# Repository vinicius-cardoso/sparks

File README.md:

# Sparks

A handheld Morse code trainer and radio transmitter.

Press the key. The device times your dots and dashes, walks the Morse tree, and
lights the letter you just formed on a 26-LED panel shaped like the tree itself.
Optionally, it keys a CC1101 and sends the same characters over the air.

The panel is the point. Instead of showing you a decoded letter as text, Sparks
shows you *where that letter lives* in the Morse tree — so the structure of the
code becomes something you read off the board rather than something you memorize
from a table.

## The LED panel

The 26 LEDs are not an arbitrary count — they are the International Morse tree for
the English alphabet, one LED per letter. All **white**, so the panel lights
uniformly.

The dot/dash distinction is carried by the **engraved panel**, not by LED colour:
the arm joining each letter to its parent is etched as a **short mark for a dot**
or a **long bar for a dash**, exactly as in `media/morse_code_guide.png`. The code
for any letter is therefore readable by tracing its path from the centre — and
stays readable with the device switched off.

Layout also follows that image: **E** and **T** sit at the centre, **dots branch
right**, **dashes branch left**, and each deeper level branches perpendicular from
its parent.

```
level 1:  E  T                                     2 LEDs
level 2:  I  A  N  M                               4 LEDs
level 3:  S  U  R  W  D  K  G  O                   8 LEDs
level 4:  H  V  F  ·  L  ·  P  J  B  X  C  Y  Z  Q  ·  ·   12 LEDs
                                                  ──────────
                                                   26 LEDs
```

A full four-level tree has 30 slots. The four marked `·` are the non-English
letters (`..--` Ü, `.-.-` Ä, `---.` Ö, `----` CH) and are left empty — deliberate
gaps in the engraved panel, not mistakes.

## Hardware

| Part | Role |
|---|---|
| ESP32-C3 Supermini | the brain — timing, decoding, radio, everything |
| MAX7219 | LED driver — constant current, 3 pins, no series resistors |
| 26 SMD LEDs | the tree panel — all white |
| CC1101 | 433 MHz transceiver (phase 2) |
| Momentary key | Morse input |
| Buzzer | sidetone, so you hear what you send |
| Li-ion cell + TP4056 | power and charging |

The MAX7219 is **not** programmable — it has no CPU. It holds which LEDs are on
and feeds them regulated current; all decisions happen on the ESP32-C3. It exists
so the panel costs 3 GPIOs instead of 26, and so the board needs **one** current-
setting resistor instead of 26 series resistors.

### Pin budget — 11 of 13 GPIOs

| Function | Pins |
|---|---|
| MAX7219 (DIN, CLK, LOAD) | 3 |
| CC1101 (SCK, MISO, MOSI, CS, GDO0) | 5 |
| Morse key | 1 |
| Buzzer | 1 |
| Battery sense (ADC) | 1 |
| **Total** | **11 — 2 spare** |

See `docs/hardware.md` for the wiring detail and the LED addressing map.

> [!NOTE]
> The MAX7219 is a 5 V part and wants ~3.5 V for a logic high. Driving it from a
> 3.3 V ESP32-C3 often works but is marginal. See `docs/hardware.md` for the two
> fixes (level shifter, or run the chip at ~4 V).

## Build phases

1. **Trainer** — LEDs + key + buzzer. No radio. Fully useful on its own, and
   nothing about it raises regulatory questions.
2. **Radio** — populate the CC1101 once the band and power limits are settled.

The CC1101 footprint is on the board from the start; phase 1 simply leaves it
unpopulated.

## Repository layout

```text
.
├── bom/          # bill of materials
├── docs/         # design decisions, hardware notes
├── firmware/     # Arduino sketch (firmware/sparks/sparks.ino)
├── hardware/     # KiCad project, datasheets
├── mechanical/   # Onshape exports, case STEP/STL
└── media/        # reference images, photos
```

## Toolchain

- **KiCad** for the PCB (`hardware/kicad/`)
- **Onshape** for the case, exported to `mechanical/`
- **Fiber laser** to engrave the copper
- **Arduino** for firmware (`firmware/sparks/`)

Keep editable sources as the source of truth: `.kicad_pro`, `.kicad_sch`,
`.kicad_pcb`, `.ino`, native CAD. Generated manufacturing output belongs in
`exports/` directories.

## Status

Early. The existing sketch (`firmware/sparks/sparks.ino`) is a CC1101 bench test
that sends a hardcoded "HELLO" — it predates the panel design and does not yet
decode input or drive the MAX7219.

## Licence

GPL-3.0 — see `LICENSE`.

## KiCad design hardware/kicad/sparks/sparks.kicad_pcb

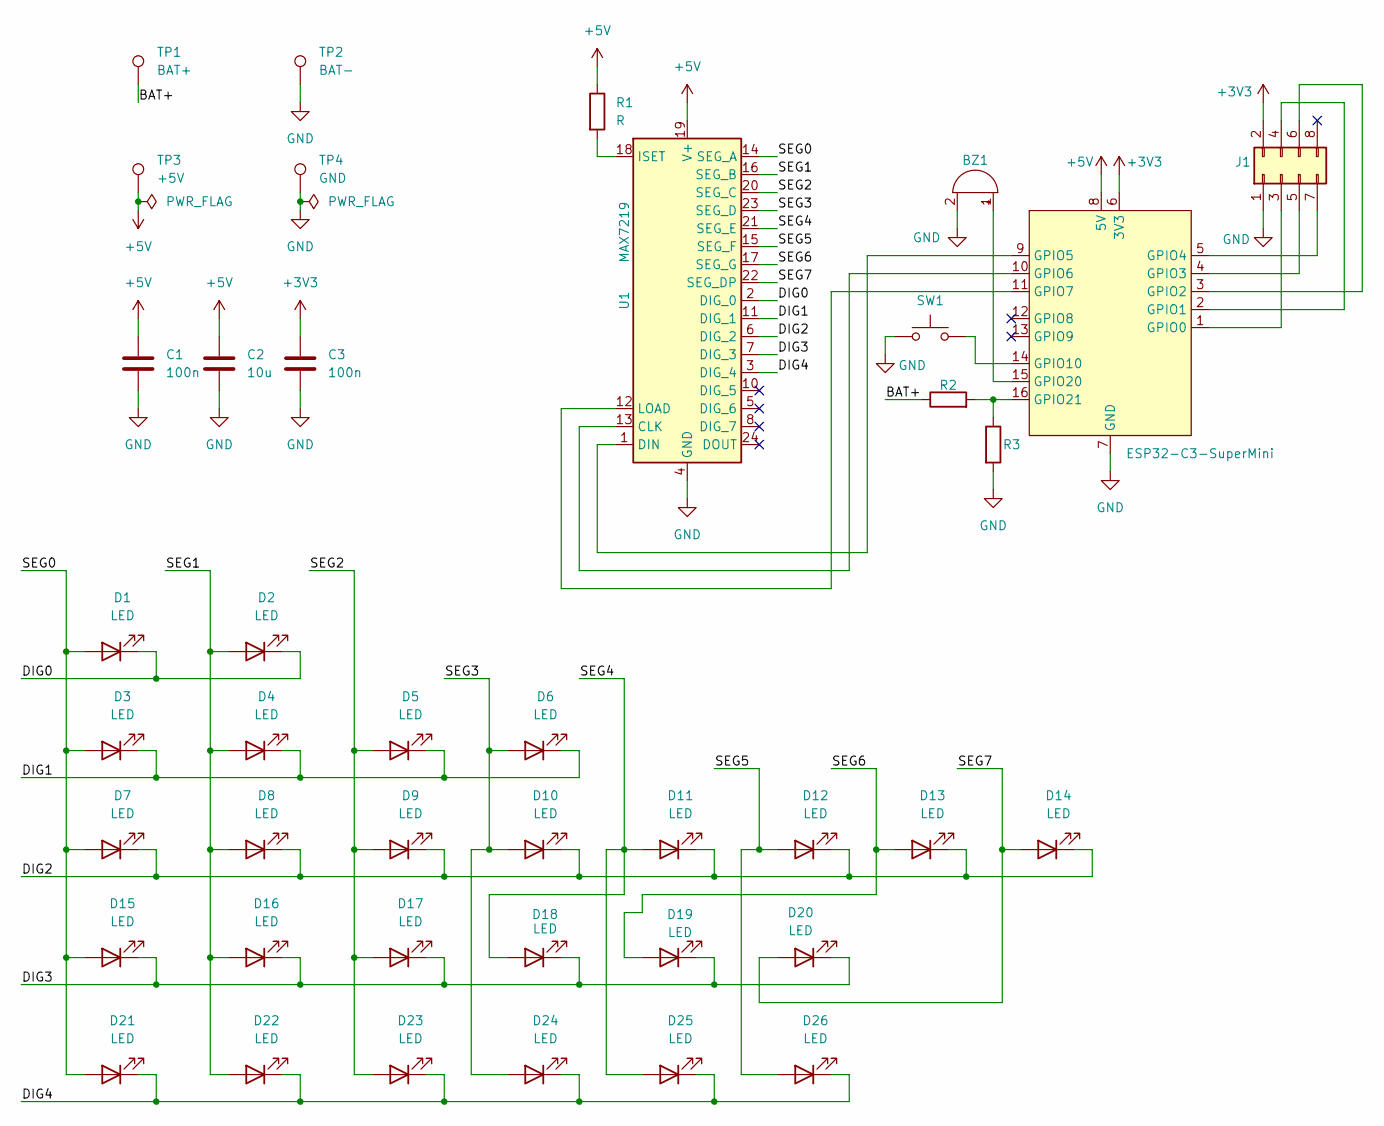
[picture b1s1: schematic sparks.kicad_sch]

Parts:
BZ1: Buzzer; Buzzer_12x9.5RM7.6
C1, C3: 100n; C_0805_2012Metric_Pad1.18x1.45mm_HandSolder
C2: 10u; C_0805_2012Metric_Pad1.18x1.45mm_HandSolder
D1, D2, D3, D4, D5, D6, D7, D8, D9, D10, D11, D12, D13, D14, D15, D16, D17, D18, D19, D20, D21, D22, D23, D24, D25, D26: LED; LED_0805_2012Metric_Pad1.15x1.40mm_HandSolder
J1: Conn_02x04_Odd_Even; PinHeader_2x04_P2.54mm_Vertical
R1: R; R_0805_2012Metric_Pad1.20x1.40mm_HandSolder
R2, R3: 220k; R_0805_2012Metric_Pad1.20x1.40mm_HandSolder
SW1: SW_Push; SW_PUSH_6mm
TP1: BAT+; TestPoint_THTPad_2.0x2.0mm_Drill1.0mm
TP2: BAT-; TestPoint_THTPad_2.0x2.0mm_Drill1.0mm
TP3: +5V; TestPoint_THTPad_2.0x2.0mm_Drill1.0mm
TP4: GND; TestPoint_THTPad_2.0x2.0mm_Drill1.0mm
U1: MAX7219; SOIC-24W_7.5x15.4mm_P1.27mm
U2: ESP32-C3-SuperMini

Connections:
+3V3: C3.1, J1.2, U2.6 (3V3)
+5V: C1.1, C2.1, R1.1, TP3.1 (1_1), U1.19 (V+), U2.8 (5V)
/BAT+: R2.1, TP1.1 (1_1)
/DIG0: D1.1 (K), D2.1 (K), U1.2 (DIG_0)
/DIG1: D3.1 (K), D4.1 (K), D5.1 (K), D6.1 (K), U1.11 (DIG_1)
/DIG2: D7.1 (K), D8.1 (K), D9.1 (K), D10.1 (K), D11.1 (K), D12.1 (K), D13.1 (K), D14.1 (K), U1.6 (DIG_2)
/DIG3: D15.1 (K), D16.1 (K), D17.1 (K), D18.1 (K), D19.1 (K), D20.1 (K), U1.7 (DIG_3)
/DIG4: D21.1 (K), D22.1 (K), D23.1 (K), D24.1 (K), D25.1 (K), D26.1 (K), U1.3 (DIG_4)
/SEG0: D1.2 (A), D3.2 (A), D7.2 (A), D15.2 (A), D21.2 (A), U1.14 (SEG_A)
/SEG1: D2.2 (A), D4.2 (A), D8.2 (A), D16.2 (A), D22.2 (A), U1.16 (SEG_B)
/SEG2: D5.2 (A), D9.2 (A), D17.2 (A), D23.2 (A), U1.20 (SEG_C)
/SEG3: D6.2 (A), D10.2 (A), D24.2 (A), U1.23 (SEG_D)
/SEG4: D11.2 (A), D18.2 (A), D25.2 (A), U1.21 (SEG_E)
/SEG5: D12.2 (A), D26.2 (A), U1.15 (SEG_F)
/SEG6: D13.2 (A), D19.2 (A), U1.17 (SEG_G)
/SEG7: D14.2 (A), D20.2 (A), U1.22 (SEG_DP)
GND: BZ1.2 (-), C1.2, C2.2, C3.2, J1.1, R3.2, SW1.1, TP2.1 (1_1), TP4.1 (1_1), U1.4 (GND), U1.9 (GND), U2.7 (GND)
unnamed: BZ1.1 (+), U2.15 (GPIO20)
unnamed: J1.3, U2.1 (GPIO0)
unnamed: J1.4, U2.2 (GPIO1)
unnamed: J1.5, U2.4 (GPIO3)
unnamed: J1.6, U2.3 (GPIO2)
unnamed: J1.7, U2.5 (GPIO4)
unnamed: U1.13 (CLK), U2.10 (GPIO6)
unnamed: U1.1 (DIN), U2.9 (GPIO5)
unnamed: R1.2, U1.18 (ISET)
unnamed: U1.12 (LOAD), U2.11 (GPIO7)
unnamed: SW1.2, U2.14 (GPIO10)
unnamed: R2.2, R3.1, U2.16 (GPIO21)

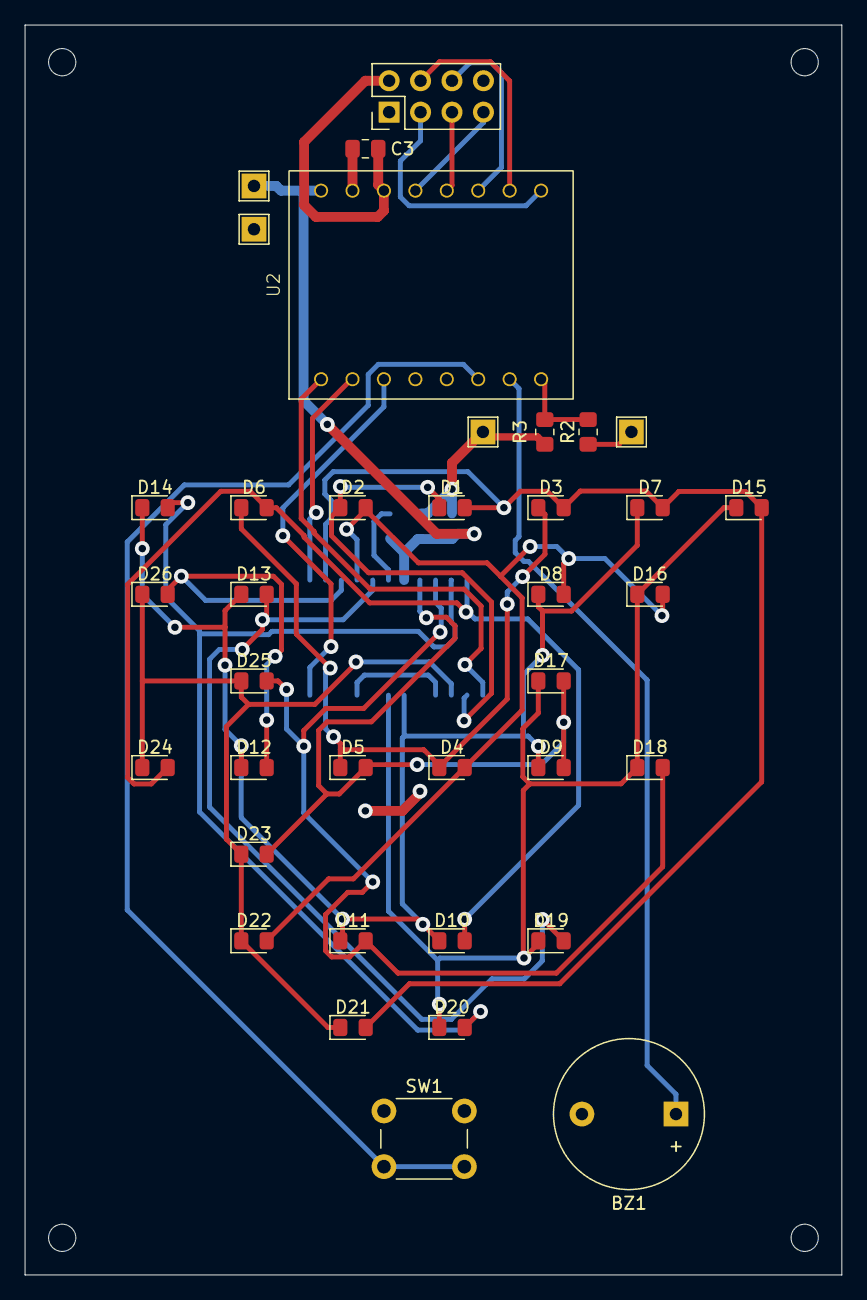
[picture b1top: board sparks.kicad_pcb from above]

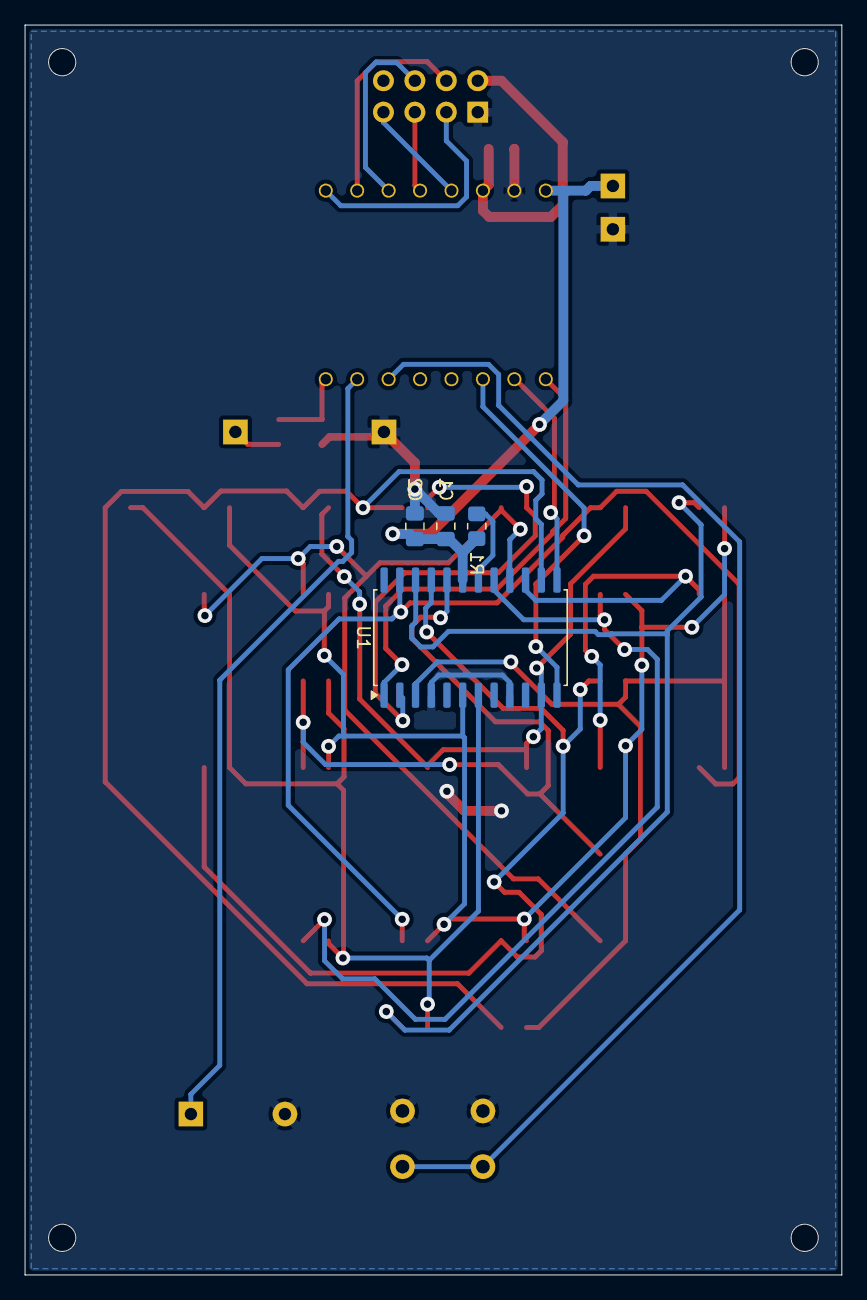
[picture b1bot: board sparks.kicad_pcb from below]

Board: 2 copper layers, 66.0 x 101.0 mm, 45 parts (4 on the bottom side), 29 nets.

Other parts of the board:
H1, H2, H3, H4: MountingHole_2.2mm_M2
